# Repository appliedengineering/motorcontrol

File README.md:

# motorcontrol
A brushed DC motor controller based on the BTN8982TA and Arduino Uno

---

<a href="https://www.infineon.com/dgdl/Infineon-Motor_Control_Shield_with_BTN8982TA_for_Arduino-UM-v01_00-EN.pdf?fileId=5546d4624ca27d02014cb20b89867eed" target="_blank">Infineon Shield Manual</a>

<a href="https://www.infineon.com/dgdl/Infineon-BTN8982TA-DS-v01_00-EN.pdf?fileId=db3a30433fa9412f013fbe32289b7c17" target="_blank">BTN8982 Datasheet</a>

<a href="https://www.infineon.com/dgdl/Infineon-NovalithIC_BTN89x0-x2-AN-v00_04-EN.pdf?fileId=db3a30433fa9412f013fc8d88e3d430a" target="_blank">BTN8982 Application Guide</a>

---

### About the PCB

The schematic and layout are completed on Upverter.
"Dual Drivers" refers to the board design intended for use with two BTN8982TA's in parallel.
Zip the Gerber files for upload to PCB fabrication services.

---

### About the Firmware

Pulse duration (µs) = (duty/100 * 1/freq) * 10^6

| Duty (%)    | PWM Freq (Hz) | Time (µs) | Prescale | OCR2A   | OCR2B  |
|-------------|---------------|-----------|----------|---------|--------|
| 1           | 1250          | 8         | /64      | 200 - 1 | 2 - 1  |
| 2           | 2500          | 8         | /32      | 200 - 1 | 4 - 1  |
| 3           | 2500          | 12        | /32      | 200 - 1 | 6 - 1  |
| 4           | 5000          | 8         | /32      | 100 - 1 | 4 - 1  |
| 5           | 5000          | 10        | /32      | 100 - 1 | 5 - 1  |
| 6           | 5000          | 12        | /32      | 100 - 1 | 6 - 1  |
| 7           | 5000          | 14        | /32      | 100 - 1 | 7 - 1  |
| 8           | 10000         | 8         | /8       | 200 - 1 | 16 - 1 |
| 9           | 10000         | 9         | /8       | 200 - 1 | 18 - 1 |
| 10          | 10000         | 10        | /8       | 200 - 1 | 20 - 1 |
| 11          | 10000         | 11        | /8       | 200 - 1 | 22 - 1 |
| 12          | 10000         | 12        | /8       | 200 - 1 | 24 - 1 |
| 13          | 10000         | 13        | /8       | 200 - 1 | 26 - 1 |
| 14          | 13333         | 10.5      | /8       | 150 - 1 | 21 - 1 |
| 15          | 16666         | 9         | /8       | 120 - 1 | 18 - 1 |
| 16          | 20000         | 8         | /8       | 100 - 1 | 16 - 1 |

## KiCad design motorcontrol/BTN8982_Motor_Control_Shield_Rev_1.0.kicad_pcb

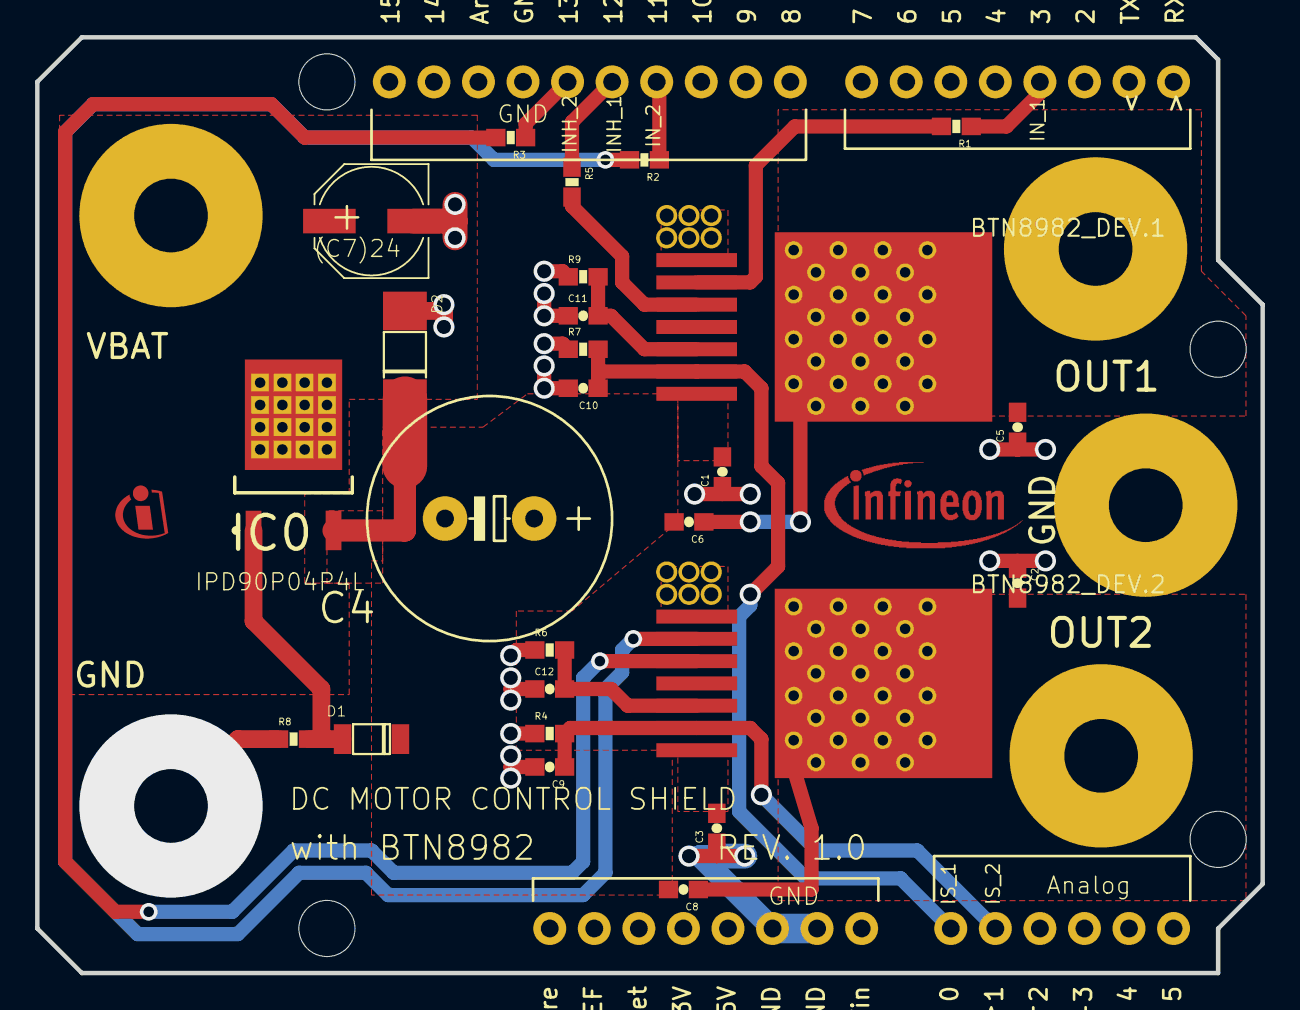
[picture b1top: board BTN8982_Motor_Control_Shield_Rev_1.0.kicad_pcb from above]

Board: 2 copper layers, 69.8 x 53.3 mm, 117 parts (0 on the bottom side), 18 nets.

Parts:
(C7)24: 100u; PANASONIC_D
BTN8982_DEV.1, BTN8982_DEV.2: HW-INFINEON_BTN8982; HW-INFINEON_TO263-7-1
C1, C3, C11, C12: 100n; 0603-CAP
C2, C5, C6, C8: 220n; 0603-CAP
C4: 1000u; RCL_E5-13
C9, C10: 1n; 0603-CAP
D1: 10V; SMD-PACKAGES_SOD80
D2: 39V; SMD-PACKAGES_MELF-D
IC0: HW_INFINEON_IPD90P04P4L-04; HW-INFINEON_TO-252-3-313-L
R1, R2, R3, R5, R8: 10k; 0603-RES
R4, R7: 1k; 0603-RES
R6, R9: 0.51k; 0603-RES
SHAPE1: ARDUINO_SHIELD; XMC1100_FOR_ARDUINO
U$1: INFINEON_LOGO_5
U$3: INFINEON_ICON_3
VP_0, VP_1, VP_2, VP_3, VP_4, VP_5, VP_6, VP_7, VP_8, VP_9, VP_10, VP_11: VPDEV0; VPAC0
VP_12, VP_41, VP_70, VP_87: VPDEV1; VPAC1
VP_13, VP_14, VP_15, VP_16, VP_17, VP_18, VP_19, VP_20, VP_21, VP_22, VP_23, VP_24, VP_25, VP_26, VP_27, VP_28, VP_29, VP_30, VP_31, VP_32, VP_33, VP_34, VP_35, VP_36, VP_37, VP_38, VP_39, VP_40, VP_42, VP_43, VP_44, VP_45, VP_46, VP_47, VP_48, VP_49, VP_50, VP_51, VP_52, VP_53, VP_54, VP_55, VP_56, VP_57, VP_58, VP_59, VP_60, VP_61, VP_62, VP_63, VP_64, VP_65, VP_66, VP_67, VP_68, VP_69: VPDEV2; VPAC2
VP_71, VP_72, VP_73, VP_74, VP_75, VP_76, VP_77, VP_78, VP_79, VP_80, VP_81, VP_82, VP_83, VP_84, VP_85, VP_86: VPDEV3; VPAC3

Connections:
A/D_1: BTN8982_DEV.1.6, C10.1, R7.2, SHAPE1.A0
A/D_2: BTN8982_DEV.2.6, C9.1, R4.2, SHAPE1.A1
GND: (C7)24.-, BTN8982_DEV.1.1, BTN8982_DEV.2.1, C1.1, C2.1, C3.1, C4.-, C5.1, C9.2, C10.2, C11.1, C12.1, D2.A, R4.1, R6.1, R7.1, R8.1, R9.1, SHAPE1.GND@0, SHAPE1.GND@1, SHAPE1.GND@2, VP_0.VP, VP_1.VP, VP_2.VP, VP_3.VP, VP_4.VP, VP_5.VP, VP_6.VP, VP_7.VP, VP_8.VP, VP_9.VP, VP_10.VP, VP_11.VP, VP_12.VP
IN1: BTN8982_DEV.1.2, R1.2
IN2: BTN8982_DEV.2.2, R2.2
INH1: BTN8982_DEV.1.3, R5.2
INH2: BTN8982_DEV.2.3, R3.2
IO_1_IN_2: R2.1, SHAPE1.D11
IO_2_IN_1: R1.1, SHAPE1.D3
IO_3_INH_2: R3.1, SHAPE1.D13
IO_4_INH_1: R5.1, SHAPE1.D12
unnamed: D1.A, IC0.P1, R8.2
OUT1: BTN8982_DEV.1.TAB, C5.2, C6.1, VP_13.VP, VP_14.VP, VP_15.VP, VP_16.VP, VP_17.VP, VP_18.VP, VP_19.VP, VP_20.VP, VP_21.VP, VP_22.VP, VP_23.VP, VP_24.VP, VP_25.VP, VP_26.VP, VP_27.VP, VP_28.VP, VP_29.VP, VP_30.VP, VP_31.VP, VP_32.VP, VP_33.VP, VP_34.VP, VP_35.VP, VP_36.VP, VP_37.VP, VP_38.VP, VP_39.VP, VP_40.VP, VP_41.VP
OUT2: BTN8982_DEV.2.TAB, C2.2, C8.1, VP_42.VP, VP_43.VP, VP_44.VP, VP_45.VP, VP_46.VP, VP_47.VP, VP_48.VP, VP_49.VP, VP_50.VP, VP_51.VP, VP_52.VP, VP_53.VP, VP_54.VP, VP_55.VP, VP_56.VP, VP_57.VP, VP_58.VP, VP_59.VP, VP_60.VP, VP_61.VP, VP_62.VP, VP_63.VP, VP_64.VP, VP_65.VP, VP_66.VP, VP_67.VP, VP_68.VP, VP_69.VP, VP_70.VP
SR1: BTN8982_DEV.1.5, C11.2, R9.2
SR2: BTN8982_DEV.2.5, C12.2, R6.2
VBAT: (C7)24.+, IC0.P2, VP_71.VP, VP_72.VP, VP_73.VP, VP_74.VP, VP_75.VP, VP_76.VP, VP_77.VP, VP_78.VP, VP_79.VP, VP_80.VP, VP_81.VP, VP_82.VP, VP_83.VP, VP_84.VP, VP_85.VP, VP_86.VP, VP_87.VP
VS: BTN8982_DEV.1.7, BTN8982_DEV.2.7, C1.2, C3.2, C4.+, C6.2, C8.2, D1.K, D2.K, IC0.P3

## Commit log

2020-02-27 Upload firmware
2020-02-27 Remove zero current detection
2020-02-27 Added configuration options
2020-02-27 Add configurations
2020-02-27 Attempt to fix sudden stopping
2020-02-28 New ramping and sanity checks
2020-02-28 Change interval type
2020-02-29 Add option to parallel outputs
2020-02-29 Throttle control
2020-02-29 Improved throttle implementation
2020-02-29 Optimize throttle control
2020-03-07 PWM bug fixes
2020-03-08 Solar features enabled
2020-03-08 Solar fixes
2020-03-09 PlatformIO Serial fix
2020-03-16 Split into separate files
2020-06-18 Update PCB and Firmware
2020-06-21 Stepped Frequency PWM
2020-06-26 Scripts for reading telemetry data
2020-06-26 Better virtualenv script
2020-06-26 Fix virtualenv script
2020-06-26 Improve script compatibility
2020-07-03 Bug fix - Error constants are class members
2020-07-03 Add PCB render
2020-07-05 Clean formatting
2020-08-02 Better current sense
2020-09-28 Begin implementing MPPT
2020-10-04 Perturb and Observe MPPT
2020-10-04 update readdata
2020-10-04 MPPT bug fix
2020-10-05 MPPT bug fix 2
2020-10-07 Begin adding UDP multicast
2020-10-08 fixes(maybe) to mppt
    Fixes to mppt that haven't been tested yet but probably work unless theres something we missed
2020-10-08 fix UDP
2020-10-08 Separate duty variables
2020-10-08 Make mppt duty variable
2020-10-08 Add throttle duty variable
2020-10-08 Fix throttle and mppt balance
2020-10-08 Add dP
2020-10-08 Bount mpptDuty
2020-10-09 Add UDP Multicast
2020-10-09 Restyled by autopep8
2020-10-09 Restyled by black
2020-10-09 Restyled by isort
2020-10-09 Restyled by yapf
2020-10-09 Add UDP Multicast (#5)
2020-10-09 Restyled/udp multicast test (#7)
    * Add UDP Multicast
    * Restyled by autopep8
    * Restyled by black
    * Restyled by isort
    * Restyled by yapf
2020-10-09 Test UDP multicast with telemetry
2020-10-11 Changes 10/11/20
2020-10-11 Changes Part 2
2020-10-12 New scripts and cleanup
2020-10-15 troubleshooting through telemetry
2020-10-16 mmpt telemetry issues
2020-10-18 Rename pub.py to print.py
2020-10-18 MessagePack and cleanup
2020-10-18 MMPT simulation test
    I don't have a power supply for my arduino so I simulated input current and voltage with
    current = 7.77*(duty/100.0)
    voltage = 13.77ln(8.77-current)
    power = current*voltage
    And it works! Mppt is stable around duty = 75
2020-10-18 Testing mode
2020-10-18 MessagePack
2020-10-18 Restyled by astyle
2020-10-18 Restyled by clang-format
2020-10-18 Restyled by whitespace
2020-10-18 Restyle Donotmerge mppt telemetry testing (#9)
    * Restyled by astyle
    * Restyled by clang-format
    * Restyled by whitespace
2020-10-18 Fix reopening port on Windows
2020-10-21 Serial end sequence fix
2020-10-23 Jump fix
    Fixes both throttle-->mppt and mppt--> throttle
2020-10-23 throttleDuty targetDuty match
2020-10-23 Add border variable
2020-10-23 Last jump fix (hopefully)
2020-10-23 Last jump fix
2020-10-23 Fix telemetry no output
2020-10-25 Fix temperature sensing blocking
2020-10-31 Update error checking
2020-10-31 Switch to dish and radio sockets
2020-11-02 Tachometer rpm and torque
2020-11-05 Fix compile errors
2020-11-18 Fix NaN and macros
2020-11-18 Fix case in telemetry
2020-11-19 Autodetect Arduino port
2020-11-23 Add timestamp to sent struct
2020-12-27 change interrupt pin
2021-01-16 Stable at constant RPM
2021-01-18 Add pyzmq readme
2021-01-18 Add documentation regarding homebrew and pyzmq
2021-01-18 Fix link + clarify a sentence
2021-01-22 Acc. test, trackTorque seems OK
2021-02-07 Best attempt for tacho & motor control on 1 arduino
2021-02-07 Add logging to txt file
2021-02-08 Add Sub compatibility + rename files
2021-02-08 Change copyright year + Add log parser
2021-02-08 Fix bug with ending comma in log_parser
2021-02-08 Fix jump, no false interrupts
    The reason there were "jumps" before was because telemetry was printing so fast sometimes it would get overloaded and just not print for a few sec
    And with the interrupts not overloading is essential, so I slowed telemetry down to only print 2x a sec
2021-02-08 Metronome test success
    Brought magnet near sensor 20x at 100bpm
    89 and 104 are fine since human error :P
2021-02-15 Add constant rpm mode
2021-02-15 Update constant rpm mode
2021-02-15 Mode for constant duty
2021-02-19 Fix constant duty mode
    makes target duty constant bc duty always chases target duty
2021-03-26 solar panel test
2021-03-26 constant current test
2021-04-25 Foot pedal test
2021-04-25 Change timestamp to unix epoch
2021-04-25 Implement floating point rounding
2021-04-26 input device settings
2021-11-16 Update install information
2021-11-16 Remove radio in transmitter script
2021-11-16 Organize log scripts
2021-11-18 Fix errors + new telemetry mode
    New telemetry mode prints values of variables to the serial monitor
2021-11-21 Change back to original telemetry mode
2021-11-22 Remove telemetry scripts
2021-11-28 Remove extra data serialization
2021-12-05 Fix throttle sensing
2021-12-06 Successful pedal test
    the motor spun + able to adjust resting speed based off how far down the pedal was pressed
